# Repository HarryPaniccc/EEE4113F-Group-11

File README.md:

# EEE4113F-Group-11
EEE4113F - Engineering System Design Group 11 Repository

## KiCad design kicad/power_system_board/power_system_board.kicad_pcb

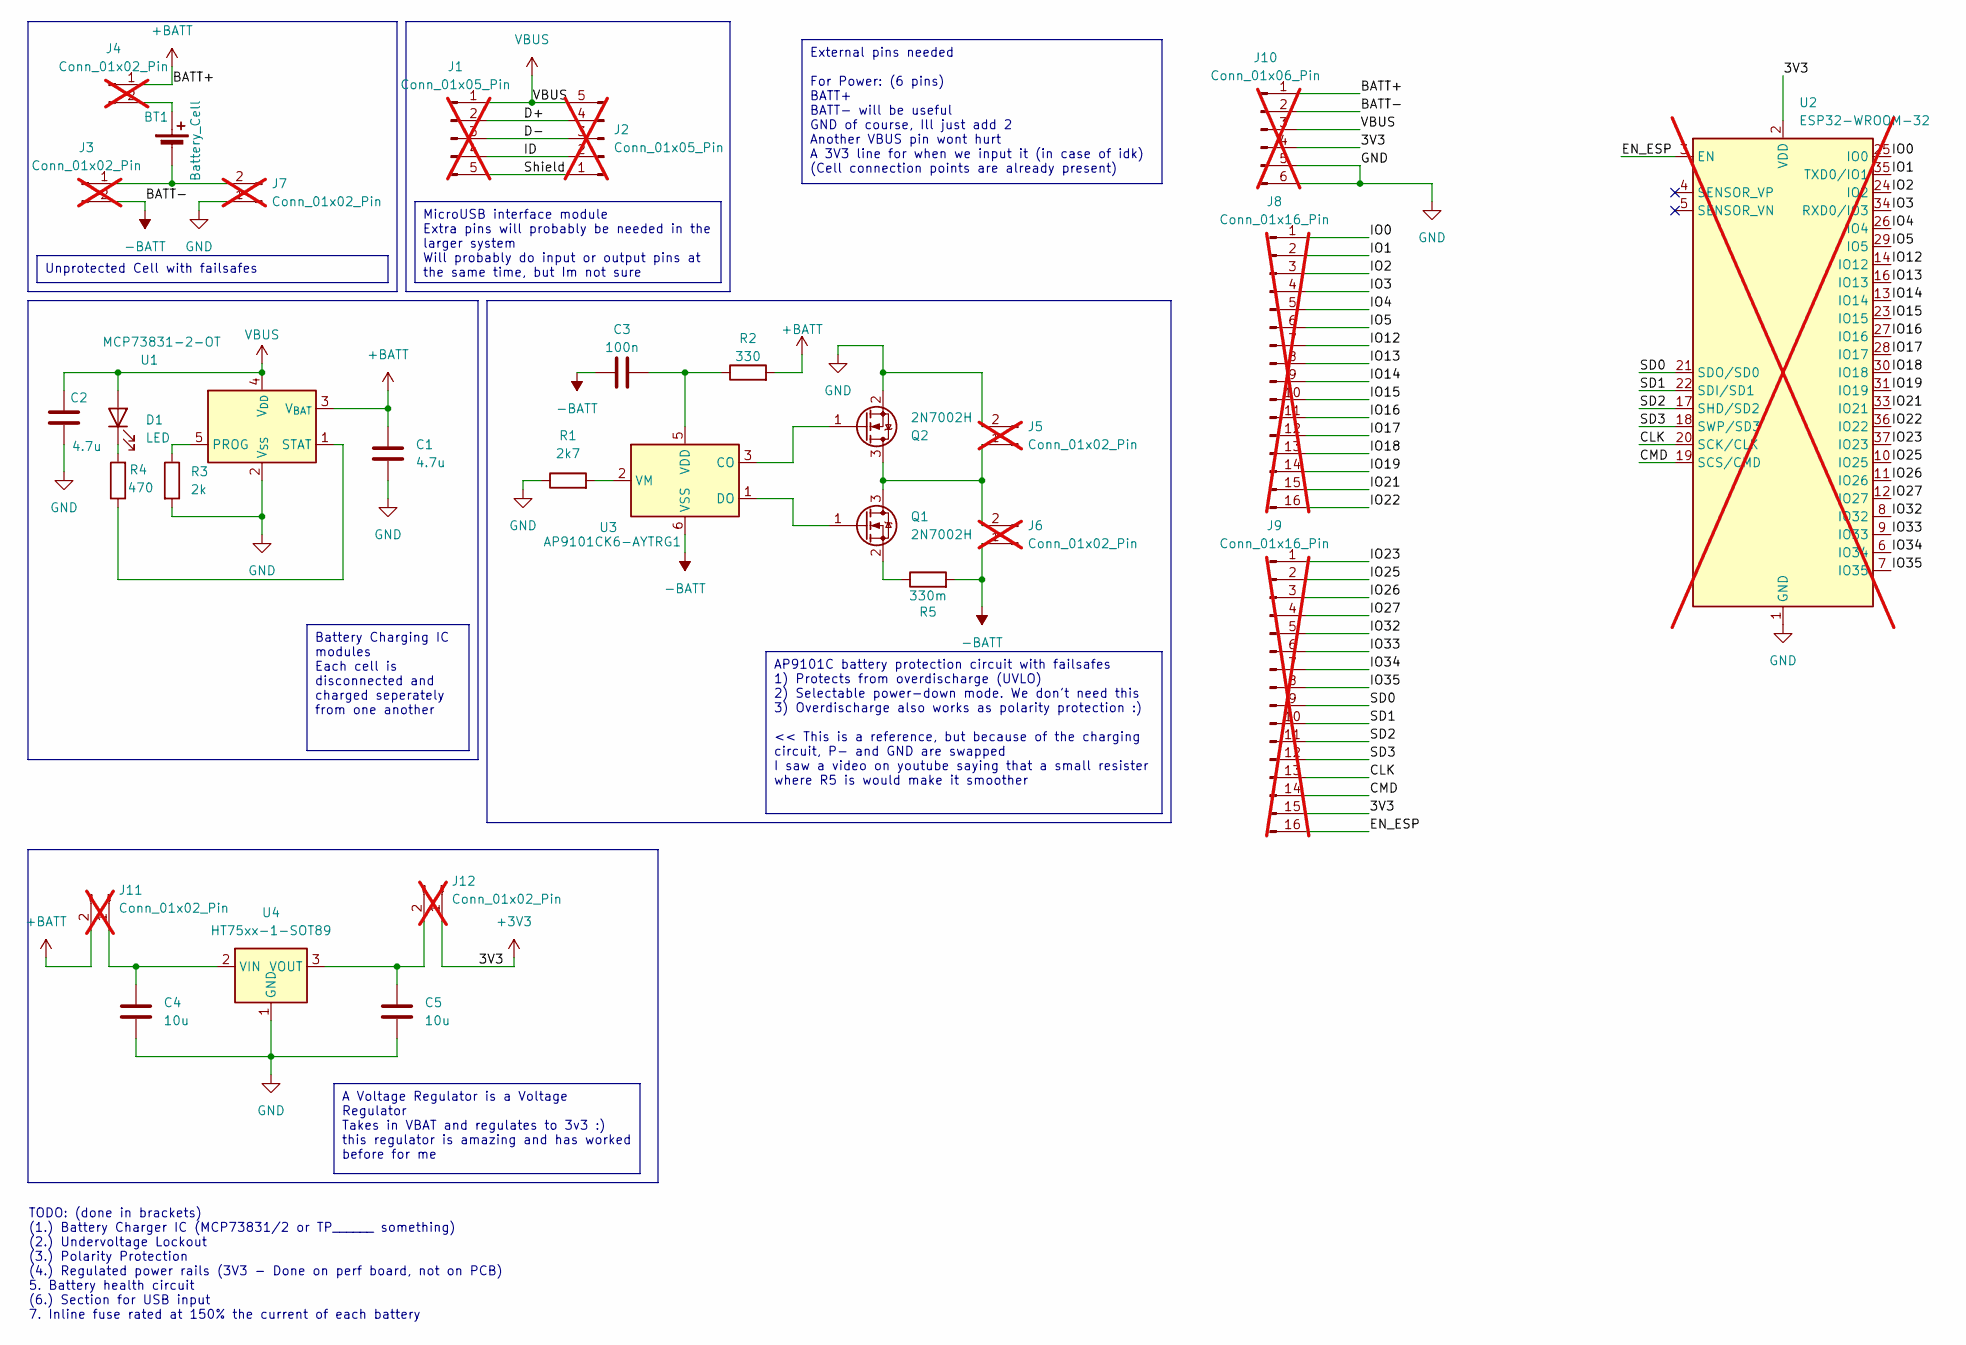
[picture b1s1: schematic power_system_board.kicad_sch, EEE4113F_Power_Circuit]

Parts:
BT1: Battery_Cell; 18650 cell holder - pin gap = 70mm
C1, C2: 4.7u; C_0805_2012Metric
C3: 100n; C_0805_2012Metric
C4, C5: 10u; C_0805_2012Metric
D1: LED; LED_0805_2012Metric
J1, J2: Conn_01x05_Pin; PinHeader_1x05_P2.54mm_Vertical; not fitted
J3, J4, J5, J6, J7, J11, J12: Conn_01x02_Pin; PinHeader_1x02_P2.54mm_Vertical; not fitted
J8, J9: Conn_01x16_Pin; PinHeader_1x16_P2.54mm_Vertical; not fitted
J10: Conn_01x06_Pin; PinHeader_1x06_P2.54mm_Vertical; not fitted
Q1, Q2: 2N7002H; SOT-23
R1: 2k7; R_0805_2012Metric
R2: 330; R_0805_2012Metric
R3: 2k; R_0805_2012Metric
R4: 470; R_0805_2012Metric
R5: 330m; R_0805_2012Metric
U1: MCP73831-2-OT; SOT-23-5
U2: ESP32-WROOM-32; not fitted
U3: AP9101CK6-AYTRG1; SOT-23-6
U4: HT75xx-1-SOT89; SOT-89-3

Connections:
+3V3: J9.15, J10.4, J12.1, U2.2 (VDD)
+BATT: C1.1, J4.1, J10.1, J11.2, R2.2, U1.3 (V_{BAT})
-BATT: C3.1, J3.2, J6.1, J10.2, R5.2, U3.6 (VSS)
/CLK: J9.13, U2.20 (SCK/CLK)
/CMD: J9.14, U2.19 (SCS/CMD)
/D+: J1.2, J2.4
/D-: J1.3, J2.3
/EN_ESP: J9.16, U2.3 (EN)
/ID: J1.4, J2.2
/IO0: J8.1, U2.25 (IO0)
/IO1: J8.2, U2.35 (TXD0/IO1)
/IO2: J8.3, U2.24 (IO2)
/IO3: J8.4, U2.34 (RXD0/IO3)
/IO4: J8.5, U2.26 (IO4)
/IO5: J8.6, U2.29 (IO5)
/IO12: J8.7, U2.14 (IO12)
/IO13: J8.8, U2.16 (IO13)
/IO14: J8.9, U2.13 (IO14)
/IO15: J8.10, U2.23 (IO15)
/IO16: J8.11, U2.27 (IO16)
/IO17: J8.12, U2.28 (IO17)
/IO18: J8.13, U2.30 (IO18)
/IO19: J8.14, U2.31 (IO19)
/IO21: J8.15, U2.33 (IO21)
/IO22: J8.16, U2.36 (IO22)
/IO23: J9.1, U2.37 (IO23)
/IO25: J9.2, U2.10 (IO25)
/IO26: J9.3, U2.11 (IO26)
/IO27: J9.4, U2.12 (IO27)
/IO32: J9.5, U2.8 (IO32)
/IO33: J9.6, U2.9 (IO33)
/IO34: J9.7, U2.6 (IO34)
/IO35: J9.8, U2.7 (IO35)
/SD0: J9.9, U2.21 (SDO/SD0)
/SD1: J9.10, U2.22 (SDI/SD1)
/SD2: J9.11, U2.17 (SHD/SD2)
/SD3: J9.12, U2.18 (SWP/SD3)
/Shield: J1.5, J2.1
GND: C1.2, C2.2, C4.2, C5.2, J5.2, J7.1, J10.5, J10.6, Q2.2 (S), R1.1, R3.2, U1.2 (V_{SS}), U2.1 (GND), U2.15 (GND), U2.38 (GND), U2.39 (GND), U4.1 (GND)
unnamed: BT1.1 (+), J4.2
unnamed: BT1.2 (-), J3.1, J7.2
unnamed: D1.1 (K), R4.2
unnamed: J5.1, J6.2, Q1.3 (D), Q2.3 (D)
unnamed: C4.1, J11.1, U4.2 (VIN)
unnamed: C5.1, J12.2, U4.3 (VOUT)
unnamed: Q1.1 (G), U3.1 (DO)
unnamed: Q1.2 (S), R5.1
unnamed: Q2.1 (G), U3.3 (CO)
unnamed: R3.1, U1.5 (PROG)
unnamed: R4.1, U1.1 (STAT)
unnamed: C3.2, R2.1, U3.5 (VDD)
unnamed: R1.2, U3.2 (VM)
VBUS: C2.1, D1.2 (A), J1.1, J2.5, J10.3, U1.4 (V_{DD})

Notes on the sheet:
A Voltage Regulator is a Voltage Regulator Takes in VBAT and regulates to 3v3 :) this regulator is amazing and has worked before for me
External pins needed For Power: (6 pins) BATT+ BATT- will be useful GND of course, Ill just add 2 Another VBUS pin wont hurt A 3V3 line for when we input it (in case of idk) (Cell connection points are already present)
AP9101C battery protection circuit with failsafes 1) Protects from overdischarge (UVLO) 2) Selectable power-down mode. We don't need this 3) Overdischarge also works as polarity protection :) << This is a reference, but because of the charging circuit, P- and GND are swapped I saw a video on youtub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
MicroUSB interface module Extra pins will probably be needed in the larger system Will probably do input or output pins at the same time, but Im not sure
Unprotected Cell with failsafes
Battery Charging IC modules Each cell is disconnected and charged seperately from one another
TODO: (done in brackets) (1.) Battery Charger IC (MCP73831/2 or TP______ something) (2.) Undervoltage Lockout (3.) Polarity Protection (4.) Regulated power rails (3V3 - Done on perf board, not on PCB) 5. Battery health circuit (6.) Section for USB input 7. Inline fuse rated at 150% the current of e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

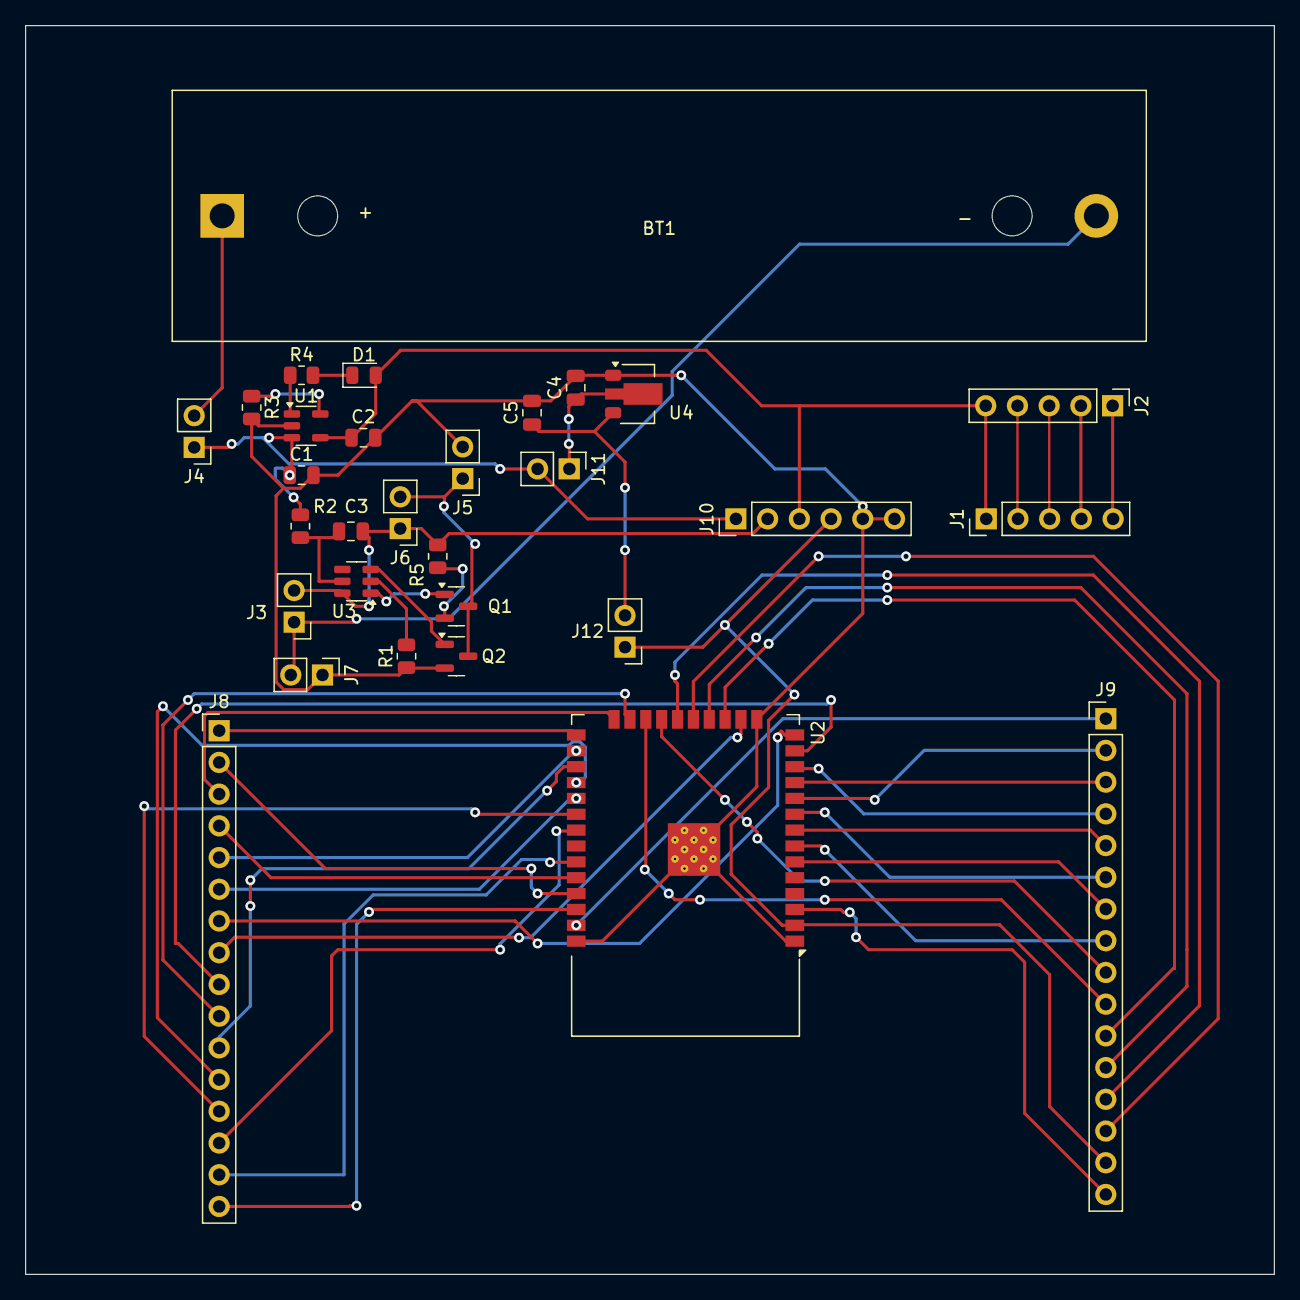
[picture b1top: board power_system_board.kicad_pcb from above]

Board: 2 copper layers, 100.0 x 100.0 mm, 30 parts (0 on the bottom side), 53 nets.

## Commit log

2024-03-10 Meeting notes from 03-10-2024
2024-04-04 kicad power project created
2024-04-04 Idea for how we could do charging
2024-04-04 Not even sure what I changed
2024-04-05 Big headway on the power module
2024-04-05 Its impossible with 2 cells
2024-04-05 Heading home after meeting
2024-04-05 Nearing end of design
2024-04-05 Checkpoint
2024-04-05 Need to add esp32 and fix USB
2024-04-05 Need to add esp32 and fix USB latest => 7:42
2024-04-05 Need to add esp32 and fix USB latest => 7:50
2024-04-05 Need to add esp32 and fix USB latest => 08:10
2024-04-05 zip file from adrian
2024-04-05 Finished schema. 1,7 hours left
2024-04-05 Checkpoinaaaaaaaaaaaat
2024-04-05 Im finished
2024-04-06 Cleaned up the kicad stuff a bit
2024-04-10 I hope everything syncs now
2024-04-10 I hate git sometimes
2024-04-10 New board design for power
2024-04-10 Finishing up for the night
2024-04-11 Parts selection and design considerations
2024-04-11 Making headway
2024-04-11 Again
2024-04-12 Pushing a few more changes so I have everything
2024-04-12 Testing some file system stuff. Addition to the power design
2024-04-13 pushing to desktop
2024-04-13 BOM updates harry
2024-04-29 Small annotation changes
2024-04-29 Value updates
2024-05-05 Pushing so everything syncs
2024-05-07 schematic changes
2024-05-08 small changes
2024-05-09 Mouse
2024-05-10 added microcontroller code
2024-05-11 Changes to circuit layout
2024-05-13 final code cleanup
2024-05-13 ammendment to final code cleanup
2024-05-14 User Interface files added
